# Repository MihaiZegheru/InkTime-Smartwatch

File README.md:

# InkTime Watch

Low-power open-source smartwatch hardware based on the **nRF52840**, designed around a **1.54” sunlight-readable e-paper display**, **BLE notifications**, **step counting**, **USB charging**, and a reliable **SWD recovery path**.

---

## Overview

InkTime is a time-first smartwatch optimized for:
- **low average power consumption**
- **high outdoor readability**
- **simple glanceable UI**
- **robust programming and recovery**
- **practical assembly for EVT/DVT prototypes**

### MVP features
- 1.54” e-paper display, **200 × 200 px**
- Partial display refresh **once per minute** for the watch face
- **BLE** notifications from a phone, with haptic alerts
- Always-on **step counting** using the accelerometer’s embedded pedometer
- **USB-C charging**
- **Tag-Connect TC2030** SWD programming/debug access

---

## Block Diagram

```text
USB-C 5V (VBUS)
   |
   v
+-------------------+
| BQ25180 Charger   |
| IN, BAT, SYS,I2C  |
+----+---------+----+
     |         |
   VBAT       VSYS
     |         |
     |         v
     |   +-------------------+
     |   | RT6160 Buck-Boost |
     |   | VIN -> 3V3        |
     |   +---------+---------+
     |             |
     v             v
+-----------+   +-------------------------------+
| MAX17048  |   | nRF52840                      |
| FuelGauge |   | BLE, USB, SPI, I2C, GPIO,SWD |
+-----+-----+   +--+---------+---------+--------+
      |            |         |         |
      |            |         |         |
      |            |         |         +--> Buttons x3
      |            |         |
      |            |         +------------> DRV2605L + ERM motor
      |            |
      |            +----------------------> BMA421 accelerometer
      |
      +-----------------------------------> Battery status / alerts

nRF52840 SPI + GPIO
        |
        v
+-------------------+
| PFET power switch |
| controls VEPD     |
+---------+---------+
          |
          v
+-------------------+
| 1.54" E-paper     |
| 200x200 display   |
+-------------------+

Tag-Connect TC2030 -> SWDIO / SWDCLK / nRESET / 3V3 / GND
```

---

## Repository Structure

```text
Hardware/
├── Schematic.sch
├── PCB.brd
└── Schematic.pdf

Manufacturing/
├── gerbers.zip
├── Bill_of_Materials.bom
└── Pick_and_Place.cpl

Mechanical/
├── InkTime-Model-Exploded.step
└── InkTime-Model.f3z

Images/
├── Exploaded.png
├── PCB.png
└── Watch.png

LICENSE
README.md
```

---

## Bill of Materials

> Main BOM items only. Passives, crystals, RF matching parts, and decoupling capacitors are listed in the exported manufacturing BOM.

| Qty | Function | Part | Ref. | JLC / LCSC | Datasheet |
|---:|---|---|---|---|---|
| 1 | MCU | nRF52840-QIAA-R | U1 | [C190794](https://jlcpcb.com/partdetail/NordicSemicon-NRF52840_QIAAR/C190794) | [Nordic Product Spec](https://docs.nordicsemi.com/bundle/ps_nrf52840/page/keyfeatures_html5.html) |
| 1 | Charger / power path | BQ25180YBGR | IC1 | [TI part page](https://www.ti.com/product/BQ25180/part-details/BQ25180YBGR) | [BQ25180 datasheet](https://www.ti.com/lit/gpn/BQ25180) |
| 1 | 3.3V regulator | RT6160AWSC | IC9 | [C7065276](https://www.lcsc.com/product-detail/C7065276.html) | [Richtek datasheet](https://www.richtek.com/Assets/product_file/RT6160A=RT6160B/DS6160AB-04.pdf) |
| 1 | Fuel gauge | MAX17048G+T10 | U3 | [C2682616](https://www.lcsc.com/product-detail/C2682616.html) | [MAX17048 datasheet](https://www.analog.com/media/en/technical-documentation/data-sheets/MAX17048-MAX17049.pdf) |
| 1 | Accelerometer | BMA421 | IC3 | [C5242966 search](https://www.jlcpcb.com/parts?searchTxt=C5242966) | [BMA421 datasheet](https://files.pine64.org/doc/datasheet/pinetime/BST-BMA421-FL000.pdf) |
| 1 | Haptic driver | DRV2605LDGSR | IC2 | [C527464](https://jlcpcb.com/partdetail/C527464) | [DRV2605L datasheet](https://www.ti.com/lit/gpn/drv2605l) |
| 1 | Vibration motor | LCM1027B3605F | M1 | [C7528806 search](https://www.jlcpcb.com/parts?searchTxt=C7528806) | [JLC search page](https://www.jlcpcb.com/parts?searchTxt=LCM1027B3605F) |
| 1 | E-paper power PFET | SI2301CDS-T1-GE3 | Q1 | [C10487](https://jlcpcb.com/partdetail/VishayIntertech-SI2301CDS_T1GE3/C10487) | [Vishay datasheet](https://www.vishay.com/docs/70209/si2301cds.pdf) |
| 1 | USB ESD protection | USBLC6-2SC6Y | D3 | [JLC search](https://www.jlcpcb.com/parts?searchTxt=USBLC6-2SC6Y) | [ST datasheet](https://www.st.com/resource/en/datasheet/usblc6-2.pdf) |
| 1 | USB-C connector | KH-TYPE-C-16P | J4 | [JLC search](https://www.jlcpcb.com/parts?searchTxt=KH-TYPE-C-16P) | [JLC search page](https://www.jlcpcb.com/parts?searchTxt=TYPE-C-16P) |
| 1 | E-paper FPC connector | 24-pin, 0.5 mm pitch | J1 | [JLC search](https://www.jlcpcb.com/parts?searchTxt=24pin%200.5mm%20FPC) | Vendor-specific |
| 1 | Debug connector footprint | Tag-Connect TC2030 | J2 | [Tag-Connect](https://www.tag-connect.com/product/tc2030-idc-nl) | [TC2030 docs](https://www.tag-connect.com/info/idc-footprint-details) |
| 3 | Buttons | SMD tactile switch | SW_UP, SW_DN, SW_ENT | [JLC search](https://www.jlcpcb.com/parts?searchTxt=EVP-AKE31A) | Vendor-specific |
| 1 | 2.4 GHz antenna | 2450AT18B100E | ANT1 | [JLC search](https://www.jlcpcb.com/parts?searchTxt=2450AT18B100E) | [Johanson datasheet](https://www.johansontechnology.com/datasheets/2450AT18B100E.pdf) |

---

## Hardware Architecture

### 1) Power tree

The board uses five main power nodes:
- **VBUS (5V):** USB input from the Type-C connector
- **VBAT:** raw LiPo battery voltage
- **VSYS:** charger system output
- **VDD_3V3:** main regulated rail from RT6160
- **VEPD:** switched display rail, enabled through a PFET

Power path:
- **USB 5V -> BQ25180 IN -> BQ25180 SYS -> RT6160 VIN -> 3.3V rail**
- **LiPo -> BQ25180 BAT**
- **LiPo -> MAX17048 BAT/VDD**

### 2) Main controller

The **nRF52840** is the main MCU and handles:
- BLE communication
- USB detection / optional USB firmware support
- SPI for the e-paper display
- I2C for low-speed peripherals
- GPIO interrupts from buttons, charger, fuel gauge, and accelerometer
- SWD programming/debug

### 3) Power-management ICs

- **BQ25180** manages USB charging and the power path.
- **RT6160** provides a stable **3.3V** rail across battery discharge.
- **MAX17048** measures battery voltage / state-of-charge directly on **VBAT**, which is more accurate than estimating charge from the 3.3V rail.

### 4) Sensors and user feedback

- **BMA421 accelerometer** is used for always-on step counting and interrupt-based wake.
- **DRV2605L** drives the vibration motor for BLE notification alerts.
- **Three buttons** provide direct user interaction and can wake the system from low-power states.

### 5) E-paper subsystem

The e-paper display is connected over **SPI** plus dedicated control lines.
A **high-side PFET** switches the display supply (**VEPD**) so the panel can be completely powered down between updates or power-cycled during recovery.

### 6) Programming and recovery

A **Tag-Connect TC2030** footprint exposes:
- **SWDIO**
- **SWDCLK**
- **nRESET**
- **3V3 reference**
- **GND**

This guarantees a reliable programming path even if the main firmware is broken.

---

## Communication Interfaces

| Interface | Connected devices |
|---|---|
| I2C | BQ25180, RT6160, MAX17048, BMA421, DRV2605L |
| SPI | E-paper display |
| USB | USB-C connector, VBUS detect, optional USB firmware path |
| SWD | TC2030 debug/programming header |
| GPIO | Buttons, interrupt lines, PFET gate, display control |

### I2C default configuration
- **SDA:** P0.06
- **SCL:** P0.07
- Pull-ups: **10 kΩ** to 3V3
- Default bus speed: **100 kHz**
- Optional validated speed: **400 kHz**

### I2C address map

| Device | Address |
|---|---:|
| BMA421 | 0x18 |
| MAX17048 | 0x36 |
| DRV2605L | 0x5A |
| BQ25180 | 0x6A |
| RT6160 | 0x75 |

---

## nRF52840 Pin Mapping

| Pin | Signal | Connected block | Reason |
|---|---|---|---|
| P0.02 | EPD_SCK | E-paper display | SPI clock |
| P0.03 | EPD_MOSI | E-paper display | SPI data out |
| P0.05 | EPD_CS | E-paper display | Dedicated chip select |
| P0.06 | I2C_SDA | Charger, regulator, fuel gauge, IMU, haptic | Shared low-speed bus |
| P0.07 | I2C_SCL | Charger, regulator, fuel gauge, IMU, haptic | Shared low-speed bus |
| P0.08 | IMU_INT1 | BMA421 | Primary wake interrupt |
| P0.12 | HAPTIC_EN | DRV2605L | Full haptic shutdown between events |
| P0.13 | BTN_UP | Button Up | Active-low user input |
| P0.14 | BTN_DN | Button Down | Active-low user input |
| P0.15 | EPD_DC | E-paper display | Data / command select |
| P0.16 | EPD_RST | E-paper display | Hardware reset |
| P0.17 | EPD_BUSY | E-paper display | Busy feedback |
| P1.00 | BTN_ENT | Enter / Esc button | Active-low user input |
| P1.01 | EPD_PWR_GATE | PFET gate | Enables VEPD power gating |
| P1.08 | IMU_INT2 | BMA421 | Secondary interrupt / debug |
| SWDIO | SWDIO | TC2030 | Programming / debug |
| SWDCLK | SWDCLK | TC2030 | Programming / debug |
| nRESET | RESET | TC2030 | Reliable recovery |
| USBDP | USB_D+ | USB-C / ESD | Native USB |
| USBDM | USB_D- | USB-C / ESD | Native USB |
| VBUS | USB_VBUS_DET | USB-C | USB attach detection |
| XC1/XC2 | 32 MHz crystal | X1 | Main radio/system clock |
| XL1/XL2 | 32.768 kHz crystal | X2 | RTC / low-power timekeeping |
| ANT | RF | Matching network + antenna | BLE antenna feed |

---

## Power Budget Notes

The product is designed around **average current reduction**, not just low peak current.

Main strategies:
- e-paper for near-zero static display power
- partial refresh once per minute instead of continuous refresh
- accelerometer used in interrupt/pedometer mode
- haptic driver disabled when idle
- optional BLE duty cycling instead of permanent active connection
- optional **VEPD** power gating through the PFET

### Validation measurements recommended during EVT
- deep-sleep current
- current during minute-tick partial refresh
- current during BLE notification event
- current during haptic event
- 24-hour average current for a realistic user profile

---

## PCB Design Notes

- **4-layer PCB recommended** for RF behavior and power integrity
- Main components placed on the **TOP** layer
- **Power traces:** minimum **0.3 mm** where possible
- **Signal traces:** minimum **0.15 mm**
- No right-angle routing
- Local **100 nF** decoupling placed close to power pins
- Ground stitching used between planes, especially near RF
- **No copper, no routing, and no ground plane under the antenna**
- Charger/regulator kept away from antenna and RF matching network
- Accelerometer placed away from the vibration motor to reduce false motion coupling
- USB differential pair routed tightly with ESD protection close to the connector
- Test pads should be clearly labeled in silkscreen

---

## Mechanical Notes

Mechanical stack:
- top lens
- e-paper module
- PCB
- battery
- vibration motor
- back cover

Design goals:
- protect the e-paper panel from bending
- align the physical enclosure buttons with PCB switches
- keep the battery away from the antenna keepout
- mechanically couple the motor to the case for better haptic transfer
- provide access to USB-C for charging and bring-up

---

## Bring-Up Checklist

1. Verify TC2030 SWD wiring.
2. Flash basic test firmware.
3. Confirm stable 3.3V rail.
4. Measure baseline sleep current.
5. Run I2C scan and detect all devices.
6. Read MAX17048 battery data.
7. Verify BQ25180 charger status.
8. Validate RT6160 output across battery range.
9. Power up the e-paper rail and test refresh.
10. Run DRV2605L motor test.
11. Validate button interrupts and debounce.
12. Validate BMA421 wake/step interrupts.

---

## Design Decisions

- **nRF52840** chosen for BLE + USB + mature tooling
- **E-paper** chosen for sunlight readability and very low average power
- **RT6160 buck-boost** used to keep the 3.3V rail stable across battery discharge
- **MAX17048** added for direct battery monitoring
- **PFET display gating** added for leakage reduction and display recovery
- **TC2030 SWD** kept mandatory for reliable bring-up and recovery

---

## Manufacturing Outputs

The final repository should include:
- native schematic and PCB files
- schematic PDF
- Gerber archive
- BOM export
- pick-and-place / CPL export
- full 3D assembly in **STEP** and **Fusion360** formats
- rendered images of the PCB and full assembly

---

## Images

```md

```

---

## License

Recommended: **Apache-2.0** or **MIT**.

---

## Submission Notes

Before submission, make sure the final repo contains:
- exact manufacturing exports
- final board screenshots/renders
- the 3D assembly
- the review issues raised during DVT
- any justified design-rule exceptions documented in GitHub issues or commit notes

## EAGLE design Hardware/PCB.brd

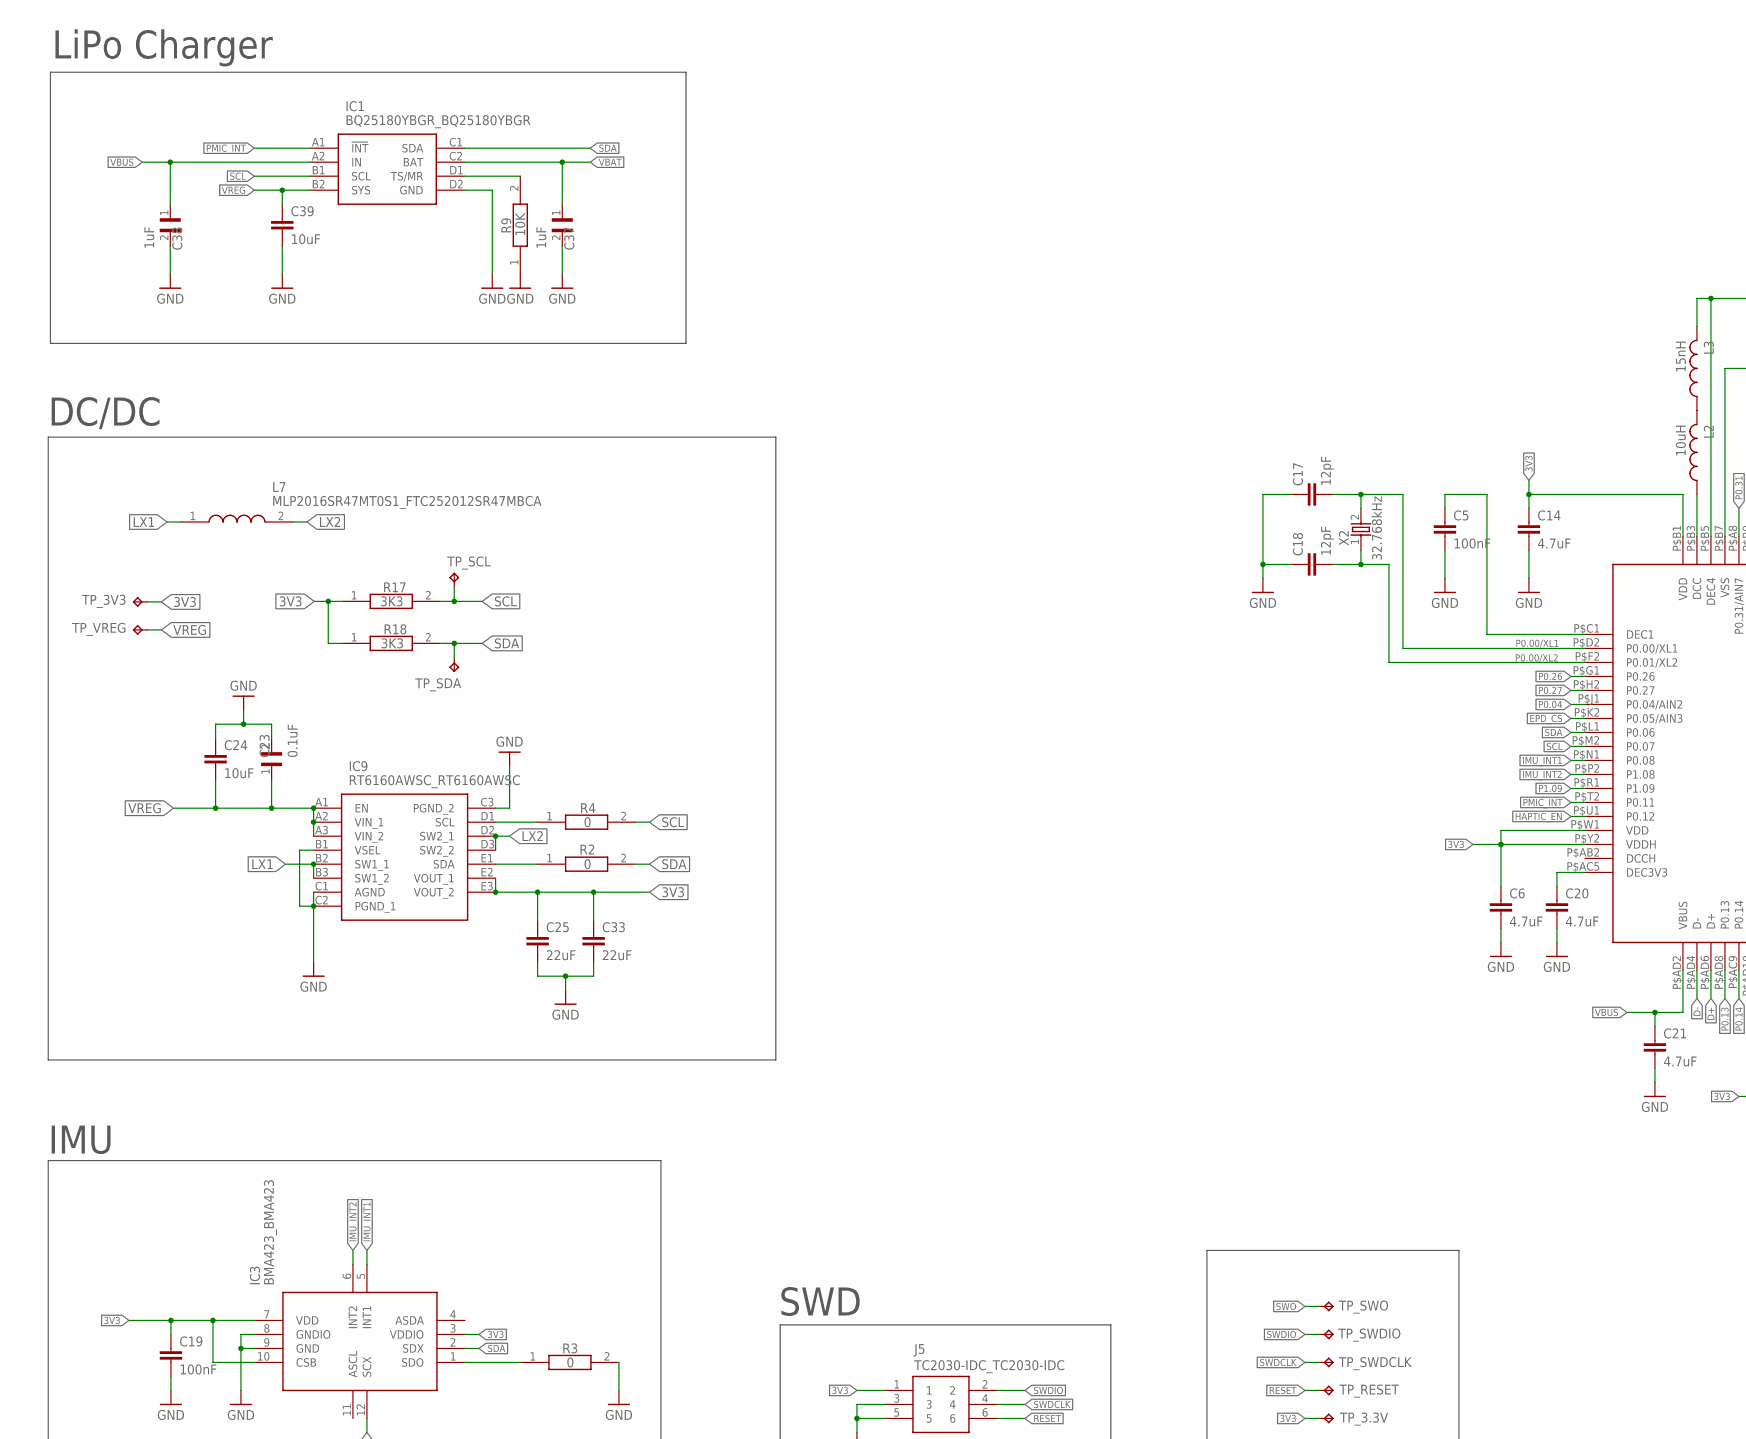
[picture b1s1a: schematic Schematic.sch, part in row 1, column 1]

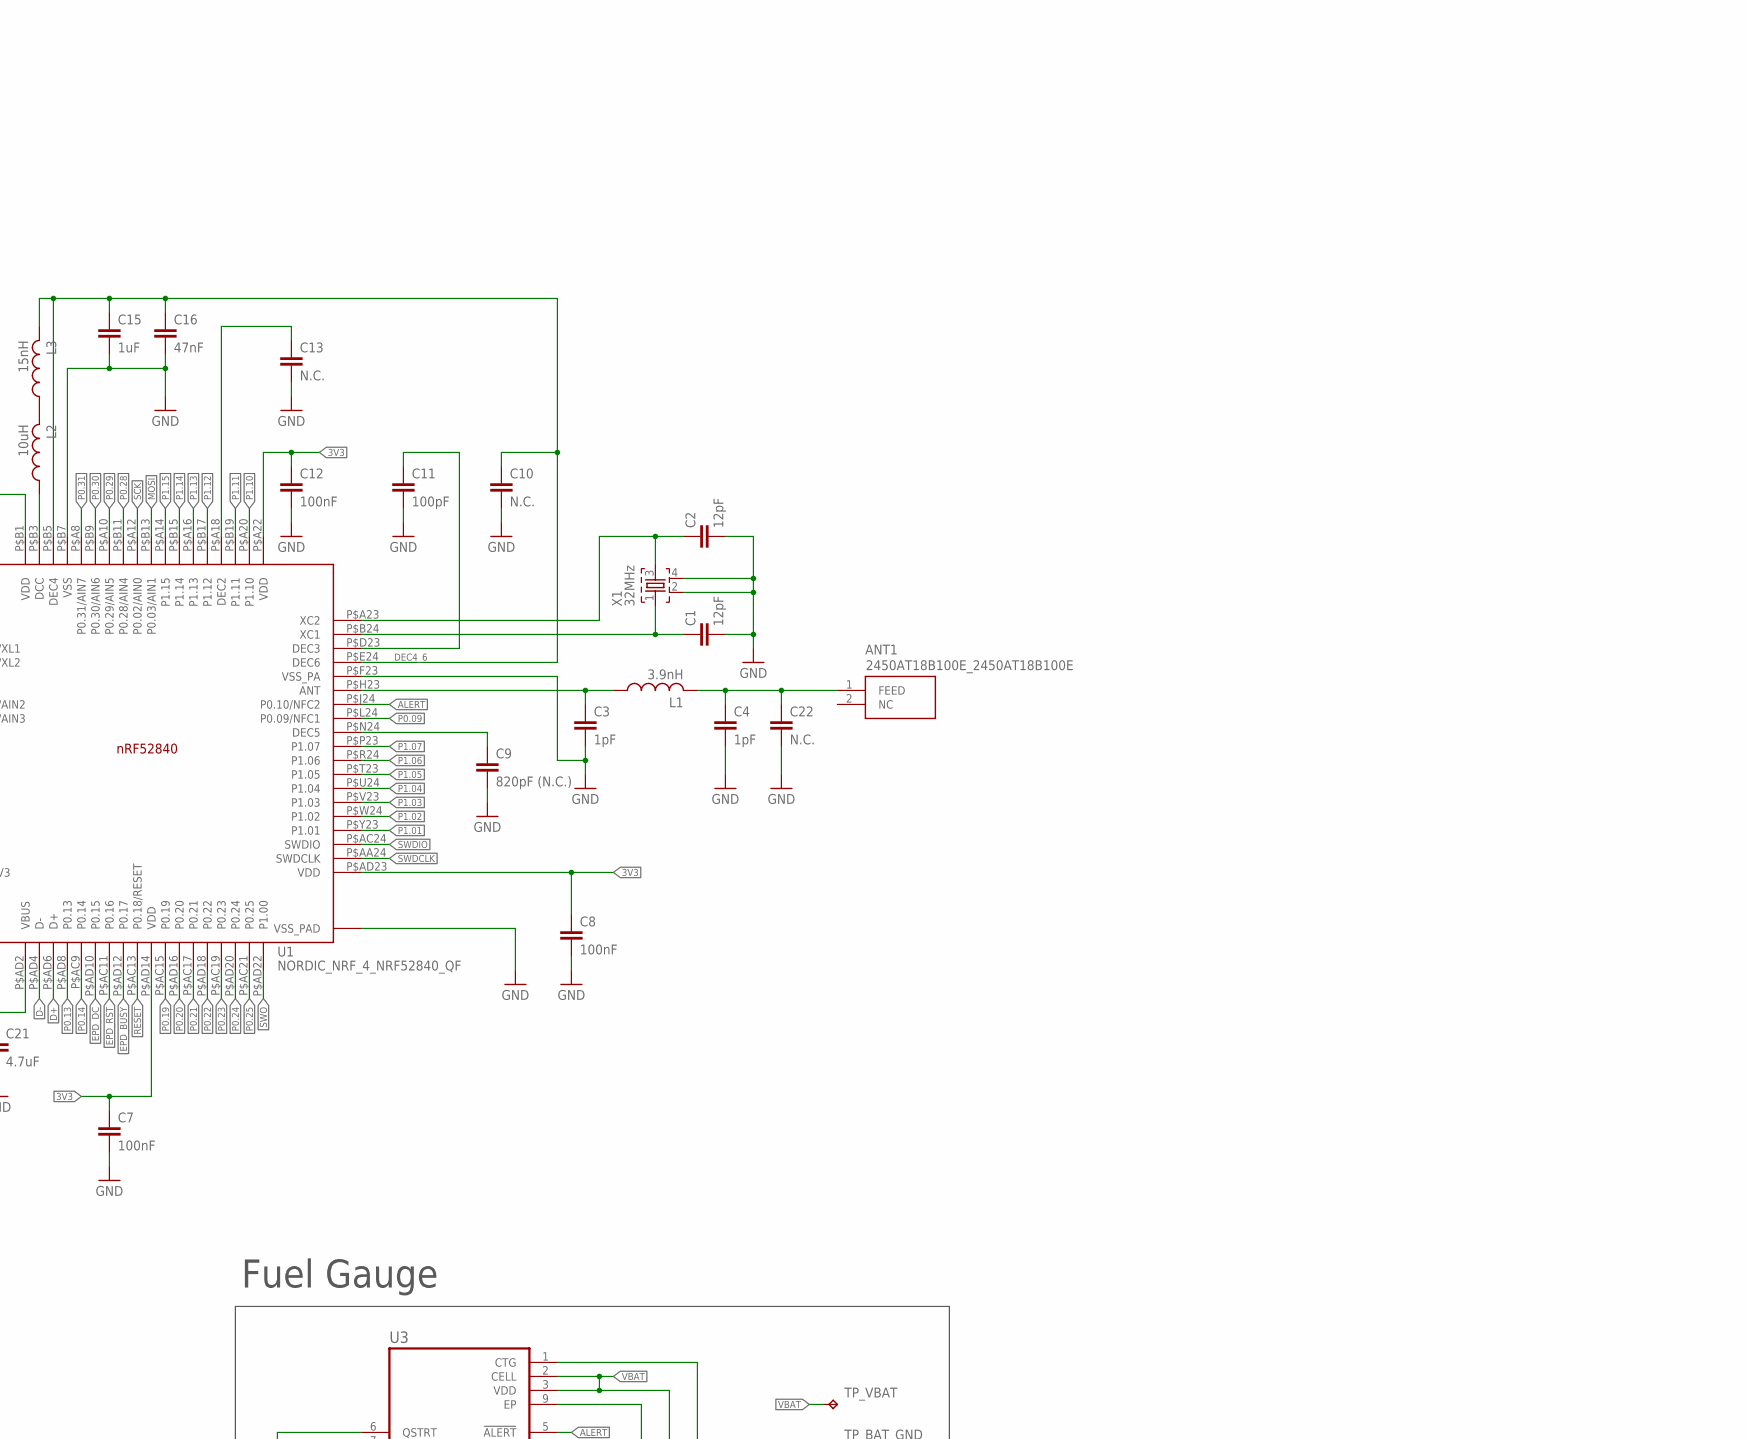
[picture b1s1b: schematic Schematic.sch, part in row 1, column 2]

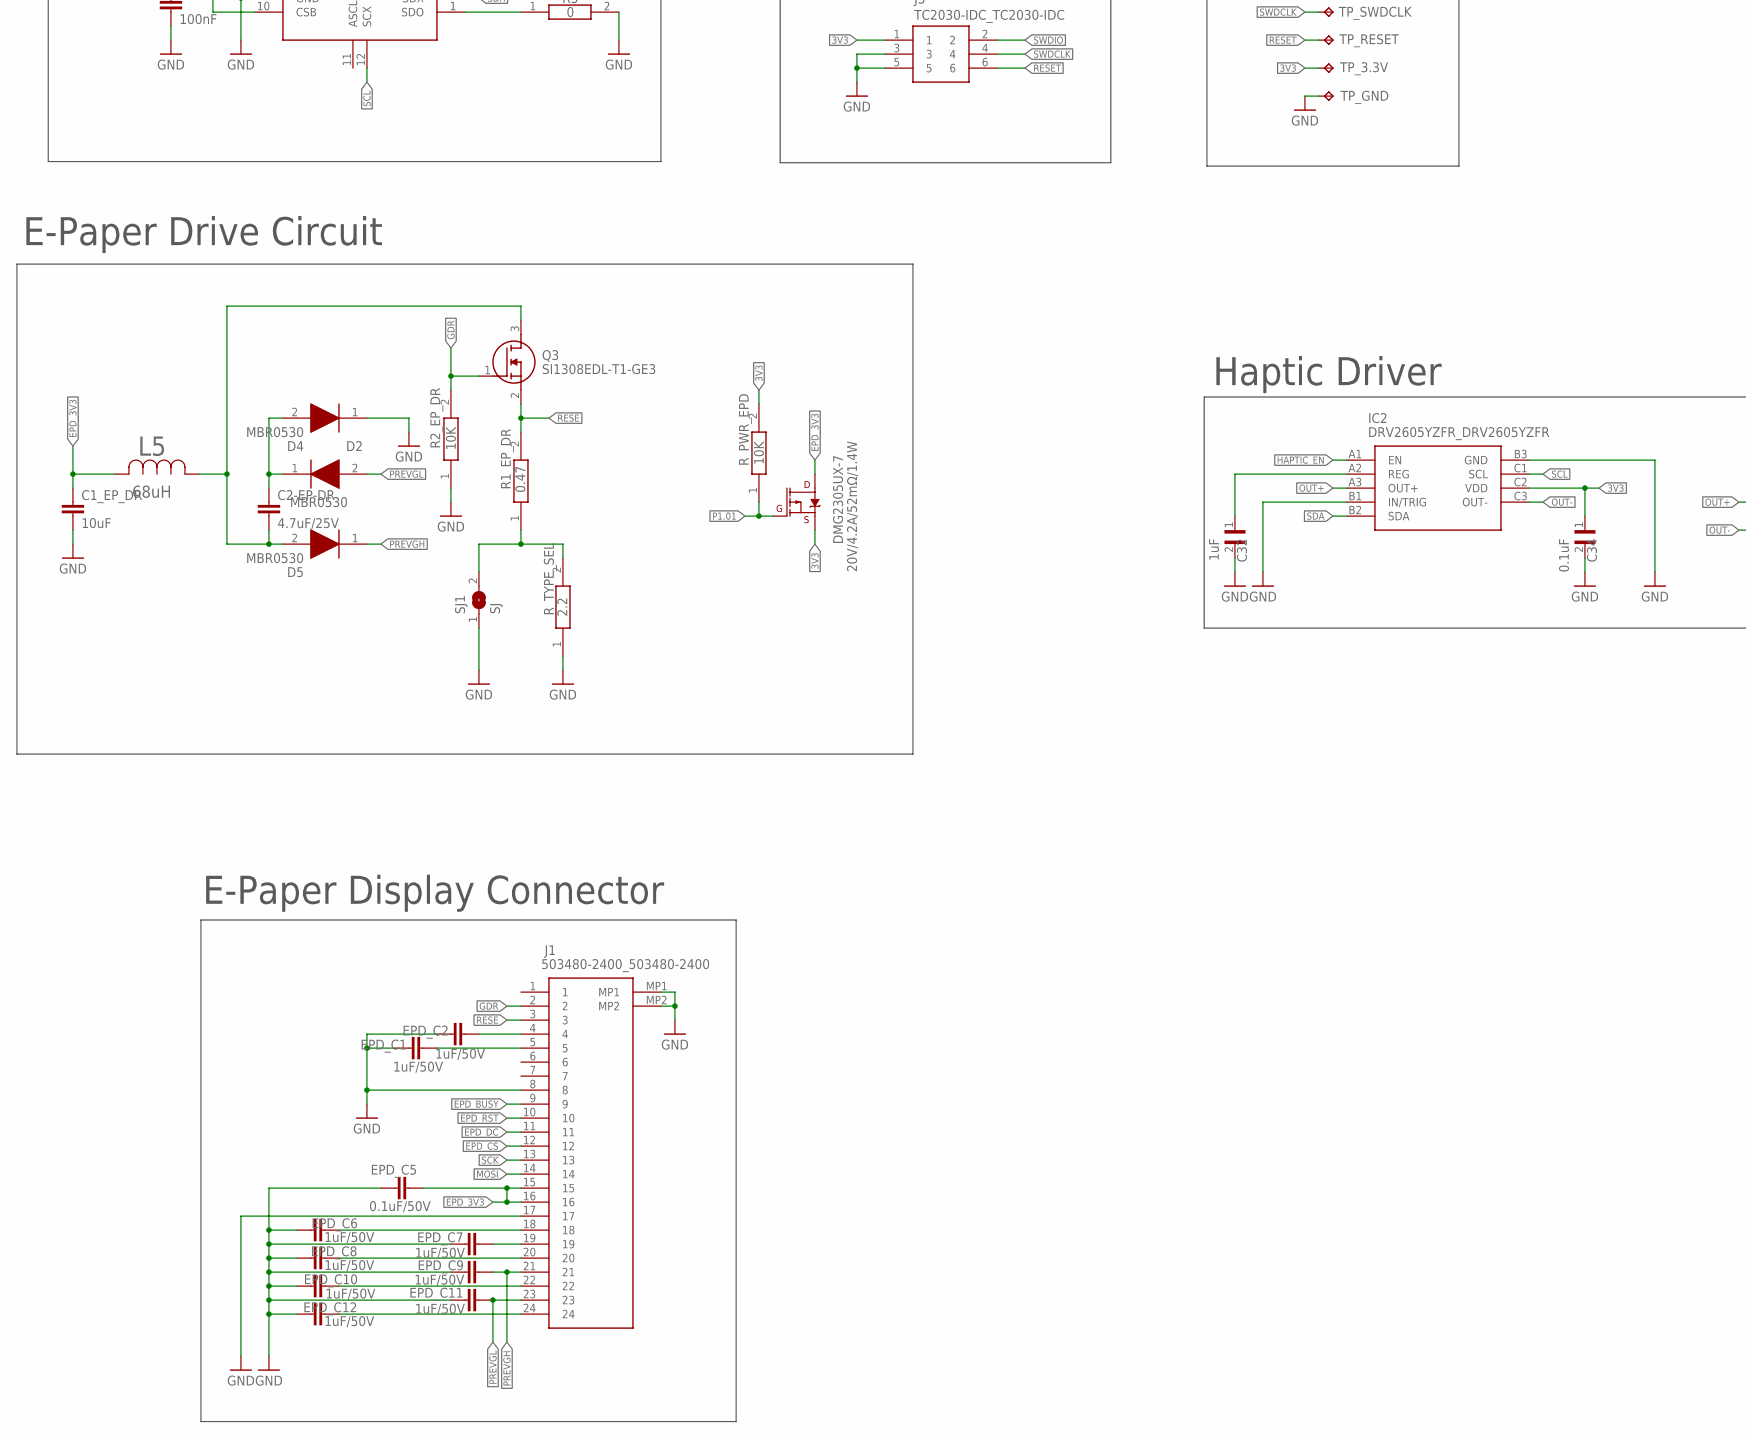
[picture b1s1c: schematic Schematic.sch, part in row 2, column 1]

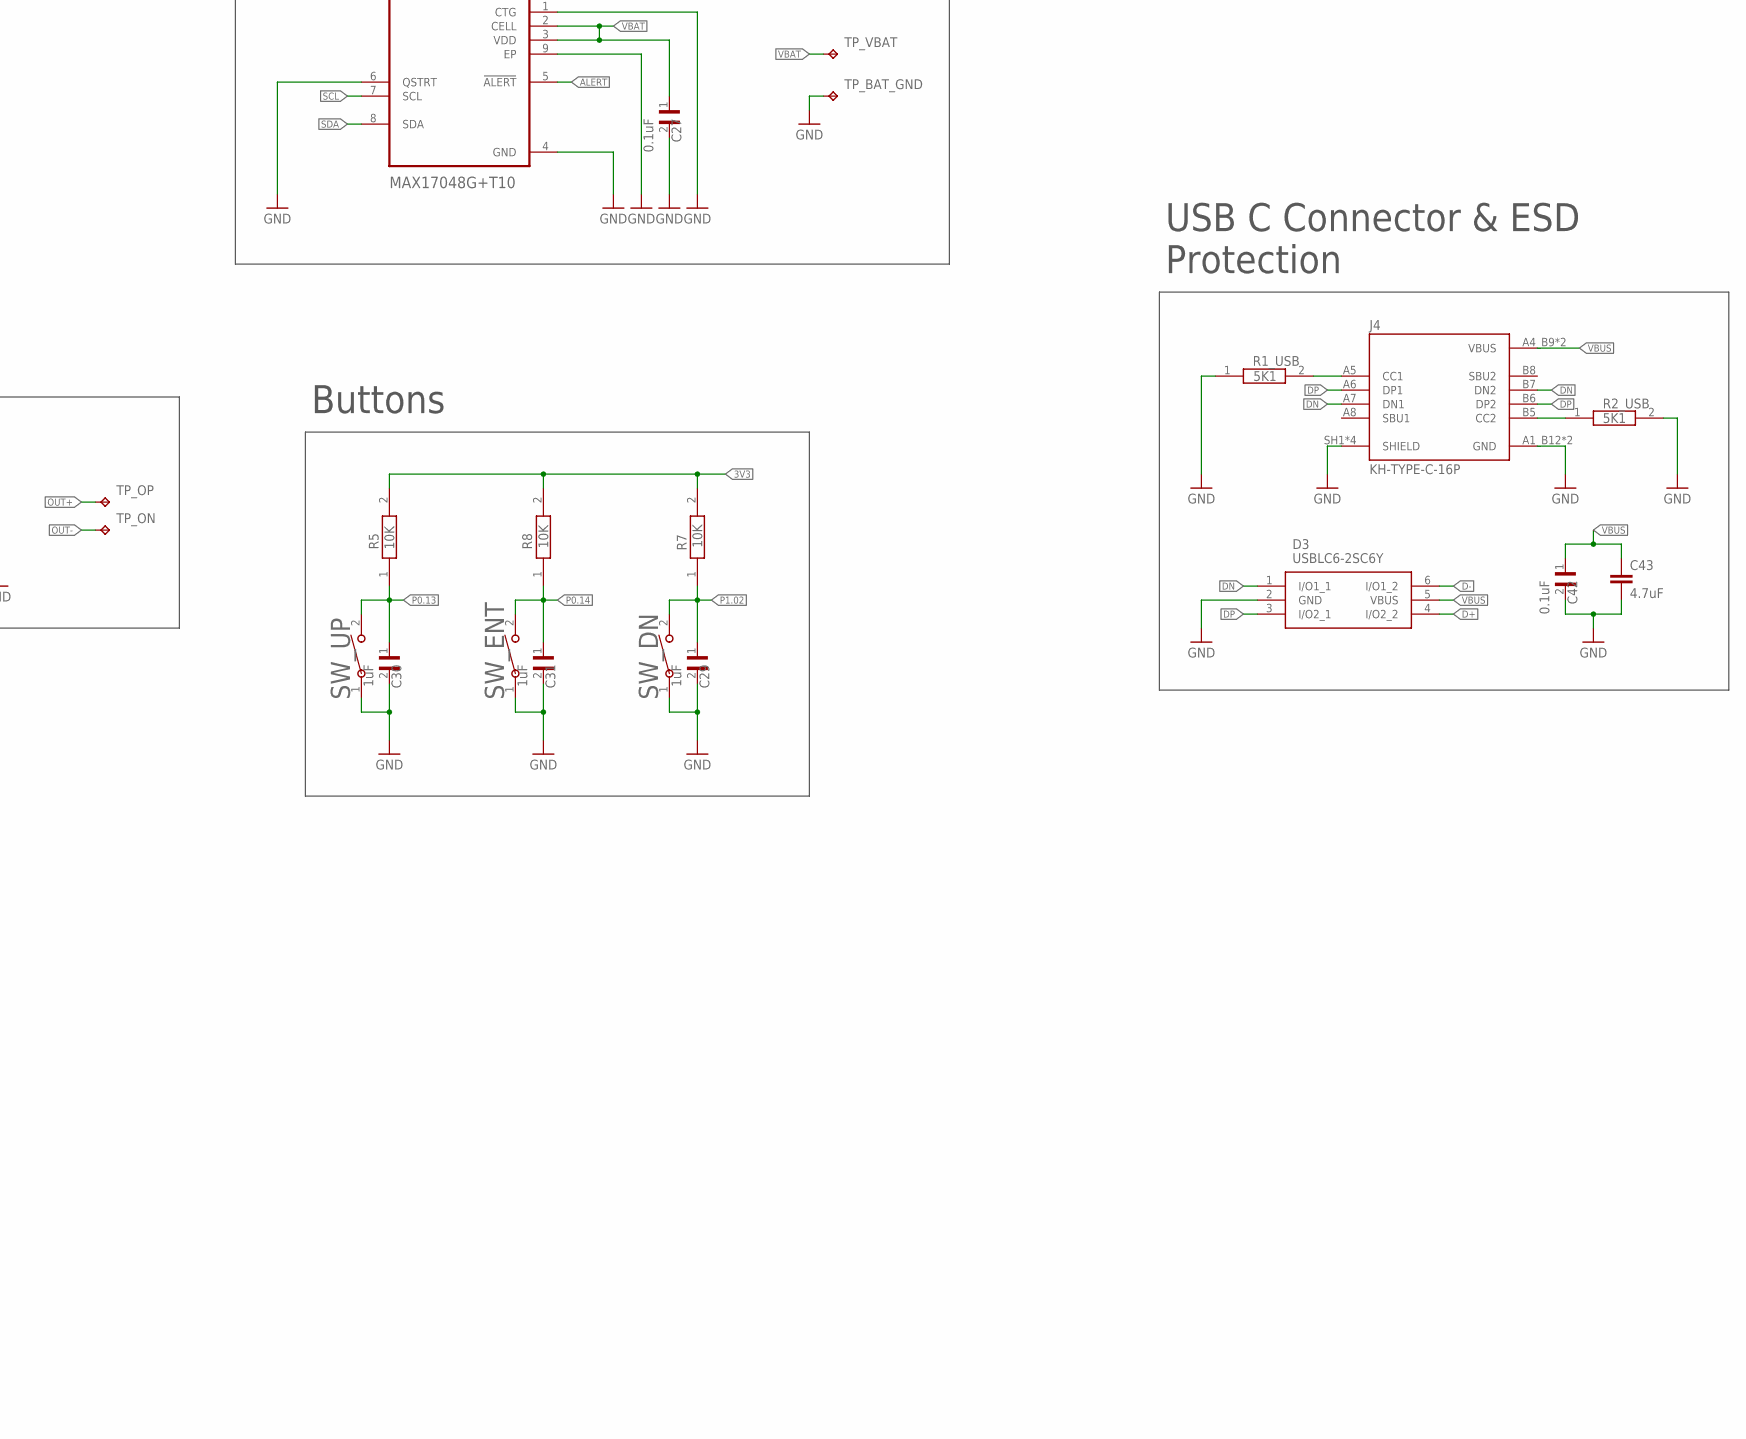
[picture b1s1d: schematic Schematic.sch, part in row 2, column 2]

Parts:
ANT1: 2450AT18B100E_2450AT18B100E; 2450AT18B100E_ANTC3216X140N
C1, C2, C17, C18: 12pF; NORDIC_NRF_3_RESC0201_L
C1_EP_DR, C24, C39: 10uF; NORDIC_NRF_3_RESC0402_L
C2-EP-DR: 4.7uF/25V; NORDIC_NRF_3_RESC0402_L
C3, C4: 1pF; NORDIC_NRF_3_RESC0201_L
C5, C7, C8, C12, C19: 100nF; NORDIC_NRF_3_RESC0201_L
C6, C14, C20, C21, C43: 4.7uF; NORDIC_NRF_3_RESC0402_L
C9: 820pF (N.C.); NORDIC_NRF_3_RESC0201_L
C10, C13, C22: N.C.; NORDIC_NRF_3_RESC0201_L
C11: 100pF; NORDIC_NRF_3_RESC0201_L
C15: 1uF; NORDIC_NRF_3_RESC0402_L
C16: 47nF; NORDIC_NRF_3_RESC0201_L
C23, C27, C34, C42: 0.1uF; GRM011R60J152KE01L_2_CAPC0201X13N
C25, C33: 22uF; NORDIC_NRF_3_RESC0402_L
C29, C30, C31, C32, C37, C38: 1uF; GRM011R60J152KE01L_2_CAPC0201X13N
D2, D4, D5: MBR0530; ESP32_C6_LIBRARY_5_SOD3716X135N
D3: USBLC6-2SC6Y; ESP32_C6_LIBRARY_3_SOT95P280X145-6N
DMG2305UX-7: 20V/4.2A/52mΩ/1.4W; ESP32_C6_LIBRARY_4_ESP32_C6_LIBRARY_4_ESP32_C6_LIBRARY_4_ES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
EPD_C1, EPD_C2, EPD_C6, EPD_C7, EPD_C8, EPD_C9, EPD_C10, EPD_C11, EPD_C12: 1uF/50V; NORDIC_NRF_3_RESC0402_L
EPD_C5: 0.1uF/50V; NORDIC_NRF_3_RESC0201_L
IC1: BQ25180YBGR_BQ25180YBGR; BQ25180YBGR_BGA8C40P2X4_100X155X50
IC2: DRV2605YZFR_DRV2605YZFR; DRV2605YZFR_BGA9C50P3X3_144X144X62
IC3: BMA423_BMA423
IC9: RT6160AWSC_RT6160AWSC; RT6160AWSC_BGA15C40P3X5_140X230X60
J1: 503480-2400_503480-2400; 503480-2400_5034802400
J4: KH-TYPE-C-16P; KH-TYPE-C-16P_KINGHELM_KH-TYPE-C-16P
J5: TC2030-IDC_TC2030-IDC; TC2030-IDC_TC2030IDC
L1: 3.9nH; NORDIC_NRF_2_RESC0201_L
L2: 10uH; NORDIC_NRF_2_RESC0402_L
L3: 15nH; NORDIC_NRF_2_RESC0201_L
L5: 68uH; ESP32_C6_LIBRARY_2_IND_4828-WE-TPC_WRE
L7: MLP2016SR47MT0S1_FTC252012SR47MBCA; MLP2016SR47MT0S1_INDC2016X100N
Q3: SI1308EDL-T1-GE3; ESP32_C6_LIBRARY_6_SOT65P210X110-3N
R1_EP_DR: 0.47; CPF0201D7K68C1_0201
R1_USB, R2_USB: 5K1; CPF0201D7K68C1_0201
R2, R3, R4: 0; CPF0201D7K68C1_0201
R2_EP_DR, R5, R7, R8, R9: 10K; CPF0201D7K68C1_0201
R17, R18: 3K3; CPF0201D7K68C1_0201
R_PWR_EPD: 10K; CPF0201D7K68C1_0201
R_TYPE_SEL: 2.2; CPF0201D7K68C1_0201
SJ1: SJ; ESP32_C6_LIBRARY_7_JUMPER_SJ
SW_DN: 2025-10-22_07-23-44_LIBRARY_EVP-AKE31ASW_EVP-AKE3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; 2025-10-22_07-23-44_LIBRARY_SW_EVP-AKE31A_PAN
SW_ENT: 2025-10-22_07-23-44_LIBRARY_EVP-AKE31ASW_EVP-AKE3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; 2025-10-22_07-23-44_LIBRARY_SW_EVP-AKE31A_PAN
SW_UP: 2025-10-22_07-23-44_LIBRARY_EVP-AKE31ASW_EVP-AKE3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; 2025-10-22_07-23-44_LIBRARY_SW_EVP-AKE31A_PAN
TP_3.3V, TP_3V3: HECTOR_WATCH_1_TPTP20R; HECTOR_WATCH_1_TP20R
TP_BAT_GND: HECTOR_WATCH_1_TPTP20R; HECTOR_WATCH_1_TP20R
TP_GND: HECTOR_WATCH_1_TPTP20R; HECTOR_WATCH_1_TP20R
TP_ON: HECTOR_WATCH_1_TPTP20R; HECTOR_WATCH_1_TP20R
TP_OP: HECTOR_WATCH_1_TPTP20R; HECTOR_WATCH_1_TP20R
TP_RESET: HECTOR_WATCH_1_TPTP20R; HECTOR_WATCH_1_TP20R
TP_SCL: HECTOR_WATCH_1_TPTP20R; HECTOR_WATCH_1_TP20R
TP_SDA: HECTOR_WATCH_1_TPTP20R; HECTOR_WATCH_1_TP20R
TP_SWDCLK: HECTOR_WATCH_1_TPTP20R; HECTOR_WATCH_1_TP20R
TP_SWDIO: HECTOR_WATCH_1_TPTP20R; HECTOR_WATCH_1_TP20R
TP_SWO: HECTOR_WATCH_1_TPTP20R; HECTOR_WATCH_1_TP20R
TP_VBAT: HECTOR_WATCH_1_TPTP20R; HECTOR_WATCH_1_TP20R
TP_VREG: HECTOR_WATCH_1_TPTP20R; HECTOR_WATCH_1_TP20R
U1: NORDIC_NRF_4_NRF52840_QF; NORDIC_NRF_4_AQFN50P700X700X85_HS-74N
U3: MAX17048G+T10; ESP32_C6_LIBRARY_SON50P200X200X80-9N
X1: 32MHz; NORDIC_NRF_BT-XTAL_2016_N
X2: 32.768kHz; NORDIC_NRF_1_XTAL_3215_N

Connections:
3V3: C6.1, C7.1, C8.1, C12.1, C14.1, C19.1, C25.1, C33.1, C34.1, DMG2305UX-7.2 (S), IC2.C2 (VDD), IC3.3 (VDDIO), IC3.7 (VDD), IC3.10 (CSB), IC9.E2 (VOUT_1), IC9.E3 (VOUT_2), J5.1, R5.2, R7.2, R8.2, R17.1, R18.1, R_PWR_EPD.2, TP_3.3V.TP, TP_3V3.TP, U1.P$A22 (VDD), U1.P$AD14 (VDD), U1.P$AD23 (VDD), U1.P$B1 (VDD), U1.P$W1 (VDD), U1.P$Y2 (VDDH)
ALERT: U1.P$J24 (P0.10/NFC2), U3.5 (!ALERT)
D+: D3.4 (I/O2_2), U1.P$AD6 (D+)
D-: D3.6 (I/O1_2), U1.P$AD4 (D-)
DEC4_6: C10.1, C15.1, C16.1, L3.2, U1.P$B5 (DEC4), U1.P$E24 (DEC6)
DN: D3.1 (I/O1_1), J4.A7 (DN1), J4.B7 (DN2)
DP: D3.3 (I/O2_1), J4.A6 (DP1), J4.B6 (DP2)
EPD_3V3: C1_EP_DR.1, DMG2305UX-7.3 (D), EPD_C5.2, J1.15, J1.16, L5.2
EPD_BUSY: J1.9, U1.P$AD12 (P0.17)
EPD_CS: J1.12, U1.P$K2 (P0.05/AIN3)
EPD_DC: J1.11, U1.P$AD10 (P0.15)
EPD_RST: J1.10, U1.P$AC11 (P0.16)
GDR: J1.2, Q3.1 (G), R2_EP_DR.2
GND: C1.2, C1_EP_DR.2, C2.2, C3.2, C4.2, C5.2, C6.2, C7.2, C8.2, C9.2, C10.2, C11.2, C12.2, C13.2, C14.2, C15.2, C16.2, C17.1, C18.1, C19.2, C20.2, C21.2, C22.2, C23.2, C24.1, C25.2, C27.2, C29.2, C30.2, C31.2, C32.2, C33.2, C34.2, C37.2, C38.2, C39.2, C42.2, C43.2, D3.2 (GND), D4.1 (K), EPD_C1.1, EPD_C2.1, EPD_C5.1, EPD_C6.1, EPD_C7.1, EPD_C8.1, EPD_C9.1, EPD_C10.1, EPD_C11.1, EPD_C12.1, IC1.D2 (GND), IC2.B1 (IN/TRIG), IC2.B3 (GND), IC3.8 (GNDIO), IC3.9 (GND), IC9.B1 (VSEL), IC9.C1 (AGND), IC9.C2 (PGND_1), IC9.C3 (PGND_2), J1.8, J1.17, J1.MP1, J1.MP2, J4.A1_B12 (GND), J4.A12_B1 (GND), J4.SH1 (SHIELD), J4.SH2 (SHIELD), J4.SH3 (SHIELD), J4.SH4 (SHIELD), J5.3, J5.5, R1_USB.1, R2_EP_DR.1, R2_USB.2, R3.2, R9.1, R_TYPE_SEL.1, SJ1.1, SW_DN.1, SW_ENT.1, SW_UP.1, TP_BAT_GND.TP, TP_GND.TP, U1.P$74 (VSS_PAD), U1.P$75 (VSS_PAD), U1.P$76 (VSS_PAD), U1.P$77 (VSS_PAD), U1.P$78 (VSS_PAD), U1.P$79 (VSS_PAD), U1.P$80 (VSS_PAD), U1.P$81 (VSS_PAD), U1.P$82 (VSS_PAD), U1.P$83 (VSS_PAD), U1.P$84 (VSS_PAD), U1.P$85 (VSS_PAD), U1.P$86 (VSS_PAD), U1.P$87 (VSS_PAD), U1.P$88 (VSS_PAD), U1.P$89 (VSS_PAD), U1.P$90 (VSS_PAD), U1.P$B7 (VSS), U1.P$F23 (VSS_PA), U3.1 (CTG), U3.4 (GND), U3.6 (QSTRT), U3.9 (EP), X1.2, X1.4
HAPTIC_EN: IC2.A1 (EN), U1.P$U1 (P0.12)
IMU_INT1: IC3.5 (INT1), U1.P$N1 (P0.08)
IMU_INT2: IC3.6 (INT2), U1.P$P2 (P1.08)
LX1: IC9.B2 (SW1_1), IC9.B3 (SW1_2), L7.1
LX2: IC9.D2 (SW2_1), IC9.D3 (SW2_2), L7.2
MOSI: J1.14, U1.P$B13 (P0.03/AIN1)
unnamed: L2.2, L3.1
unnamed: IC9.D1 (SCL), R4.1
unnamed: C32.1, IC2.A2 (REG)
unnamed: IC9.E1 (SDA), R2.1
unnamed: IC3.1 (SDO), R3.1
unnamed: C5.1, U1.P$C1 (DEC1)
unnamed: IC1.D1 (TS/MR), R9.2
unnamed: C2-EP-DR.1, D2.1 (K), D4.2 (A)
unnamed: EPD_C6.2, J1.18
unnamed: R1_EP_DR.1, R_TYPE_SEL.2, SJ1.2
unnamed: J4.A5 (CC1), R1_USB.2
unnamed: EPD_C2.2, J1.4
unnamed: EPD_C1.2, J1.5
unnamed: J4.B5 (CC2), R2_USB.1
unnamed: EPD_C7.2, J1.19
unnamed: C2-EP-DR.2, D5.2 (A), L5.1, Q3.3 (D)
unnamed: C20.1, U1.P$AC5 (DEC3V3)
unnamed: EPD_C8.2, J1.20
unnamed: EPD_C12.2, J1.24
unnamed: EPD_C10.2, J1.22
unnamed: L2.1, U1.P$B3 (DCC)
unnamed: C13.1, U1.P$A18 (DEC2)
unnamed: C9.1, U1.P$N24 (DEC5)
unnamed: C11.1, U1.P$D23 (DEC3)
unnamed: C2.1, U1.P$A23 (XC2), X1.3
unnamed: C1.1, U1.P$B24 (XC1), X1.1
unnamed: C3.1, L1.1, U1.P$H23 (ANT)
unnamed: ANT1.1 (FEED), C4.1, C22.1, L1.2
OUT+: IC2.A3 (OUT+), TP_OP.TP
OUT-: IC2.C3 (OUT-), TP_ON.TP
P0.00/XL1: C17.2, U1.P$D2 (P0.00/XL1), X2.2
P0.00/XL2: C18.2, U1.P$F2 (P0.01/XL2), X2.1
P0.04: U1.P$J1 (P0.04/AIN2)
P0.09: U1.P$L24 (P0.09/NFC1)
P0.13: C30.1, R5.1, SW_UP.2, U1.P$AD8 (P0.13)
P0.14: C31.1, R8.1, SW_ENT.2, U1.P$AC9 (P0.14)
P0.19: U1.P$AC15 (P0.19)
P0.20: U1.P$AD16 (P0.20)
P0.21: U1.P$AC17 (P0.21)
P0.22: U1.P$AD18 (P0.22)
P0.23: U1.P$AC19 (P0.23)
P0.24: U1.P$AD20 (P0.24)
P0.25: U1.P$AC21 (P0.25)
P0.26: U1.P$G1 (P0.26)
P0.27: U1.P$H2 (P0.27)
P0.28: U1.P$B11 (P0.28/AIN4)
P0.29: U1.P$A10 (P0.29/AIN5)
P0.30: U1.P$B9 (P0.30/AIN6)
P0.31: U1.P$A8 (P0.31/AIN7)
P1.01: DMG2305UX-7.1 (G), R_PWR_EPD.1, U1.P$Y23 (P1.01)
P1.02: C29.1, R7.1, SW_DN.2, U1.P$W24 (P1.02)
P1.03: U1.P$V23 (P1.03)
P1.04: U1.P$U24 (P1.04)
P1.05: U1.P$T23 (P1.05)
P1.06: U1.P$R24 (P1.06)
P1.07: U1.P$P23 (P1.07)
P1.09: U1.P$R1 (P1.09)
P1.10: U1.P$A20 (P1.10)
P1.11: U1.P$B19 (P1.11)
P1.12: U1.P$B17 (P1.12)
P1.13: U1.P$A16 (P1.13)
P1.14: U1.P$B15 (P1.14)
P1.15: U1.P$A14 (P1.15)
PMIC_INT: IC1.A1 (!INT), U1.P$T2 (P0.11)
PREVGH: D5.1 (K), EPD_C9.2, J1.21
PREVGL: D2.2 (A), EPD_C11.2, J1.23
RESE: J1.3, Q3.2 (S), R1_EP_DR.2
RESET: J5.6, TP_RESET.TP, U1.P$AC13 (P0.18/RESET)
SCK: J1.13, U1.P$A12 (P0.02/AIN0)
SCL: IC1.B1 (SCL), IC2.C1 (SCL), IC3.12 (SCX), R4.2, R17.2, TP_SCL.TP, U1.P$M2 (P0.07), U3.7 (SCL)
SDA: IC1.C1 (SDA), IC2.B2 (SDA), IC3.2 (SDX), R2.2, R18.2, TP_SDA.TP, U1.P$L1 (P0.06), U3.8 (SDA)
SWDCLK: J5.4, TP_SWDCLK.TP, U1.P$AA24 (SWDCLK)
SWDIO: J5.2, TP_SWDIO.TP, U1.P$AC24 (SWDIO)
SWO: TP_SWO.TP, U1.P$AD22 (P1.00)
VBAT: C27.1, C37.1, IC1.C2 (BAT), TP_VBAT.TP, U3.2 (CELL), U3.3 (VDD)
VBUS: C21.1, C38.1, C42.1, C43.1, D3.5 (VBUS), IC1.A2 (IN), J4.A4_B9 (VBUS), J4.A9_B4 (VBUS), U1.P$AD2 (VBUS)
VREG: C23.1, C24.2, C39.1, IC1.B2 (SYS), IC9.A1 (EN), IC9.A2 (VIN_1), IC9.A3 (VIN_2), TP_VREG.TP

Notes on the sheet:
DC/DC
LiPo Charger
IMU
SWD
E-Paper Drive Circuit
Haptic Driver
Fuel Gauge
Buttons
USB C Connector & ESD Protection
E-Paper Display Connector

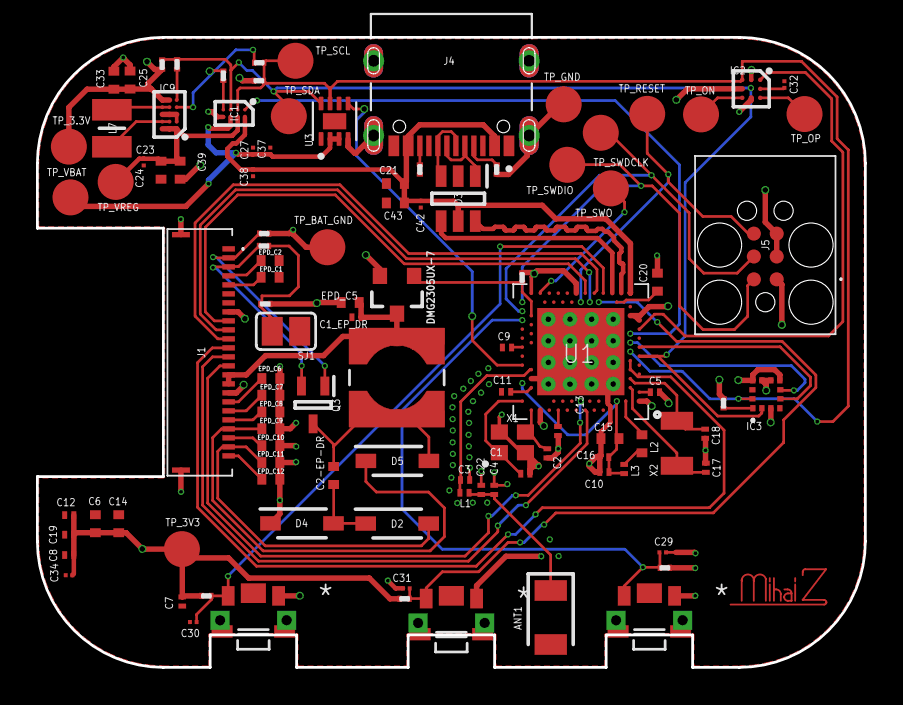
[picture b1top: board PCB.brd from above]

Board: 4 copper layers, 46.0 x 35.0 mm, 105 parts (0 on the bottom side), 70 nets.

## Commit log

2026-04-10 Initial=Final Solution
2026-04-16 Add Schematic print-out
2026-04-17 Fix unrouted airwires for ANT1 and U1
2026-04-17 Update README.md - fix #4
2026-04-18 Add 3D models for components and update all impacted files - fix #3

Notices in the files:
parts and their libraries:
COPYRIGHT: Copyright (C) 2024 Ultra Librarian. All rights reserved.
COPYRIGHT: Copyright (C) 2025 Ultra Librarian. All rights reserved.
